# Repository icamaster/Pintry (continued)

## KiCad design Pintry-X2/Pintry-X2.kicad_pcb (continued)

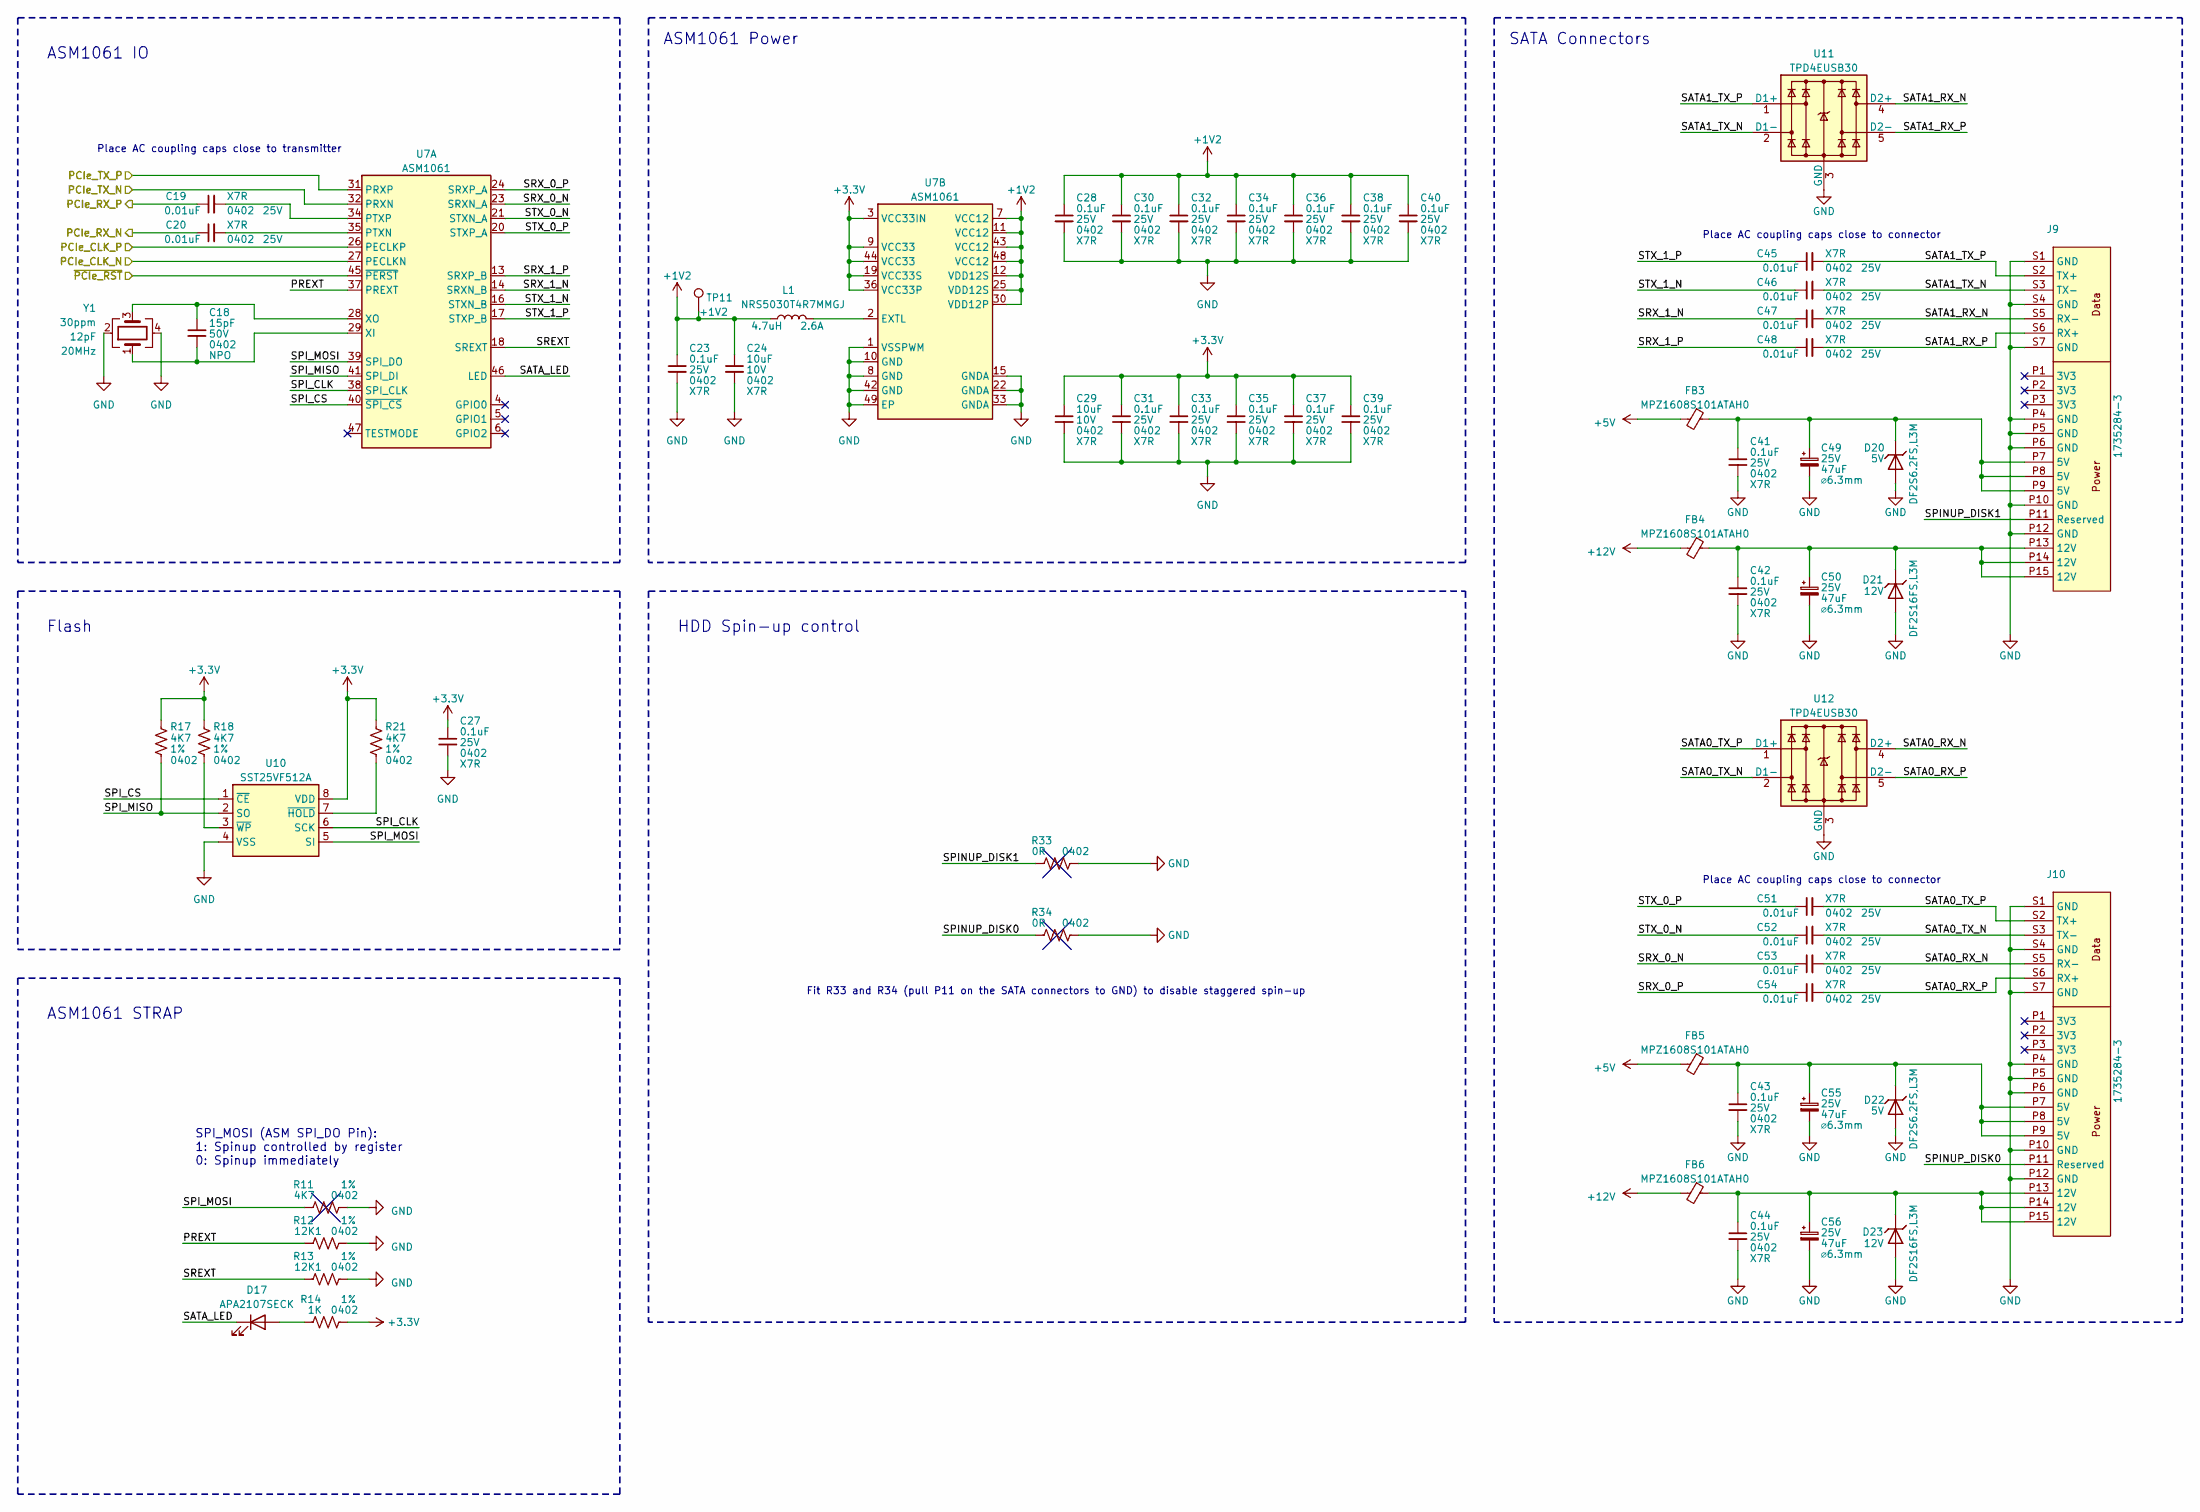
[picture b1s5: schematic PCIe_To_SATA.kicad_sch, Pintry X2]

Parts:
C18: 15pF; C_0402_1005Metric; Voltage Rating 50V
C19, C20, C45, C46, C47, C48, C51, C52, C53, C54: 0.01uF; C_0402_1005Metric; Voltage Rating 25V
C23, C27, C28, C30, C31, C32, C33, C34, C35, C36, C37, C38, C39, C40, C41, C42, C43, C44: 0.1uF; C_0402_1005Metric; Voltage Rating 25V
C24, C29: 10uF; C_0402_1005Metric; Voltage Rating 10V
C49, C50, C55, C56: 865080443007; CP_Elec_6.3x5.4; Voltage 25V; Part Number 865080443007
D17: APA2107SECK; PartNumber APA2107SECK/J4-PRV
D20, D22: DF2S6.2FS,L3M; D_SOD-923; Part Number DF2S6.2FS,L3M
D21, D23: DF2S16FS,L3M; D_SOD-923; Part Number DF2S16FS,L3M
FB3, FB4, FB5, FB6: MPZ1608S101ATAH0; L_0603_1608Metric; Part Number MPZ1608S101ATAH0
J9, J10: 1735284-3; TE_1735284-3; Part Number 1735284-3
L1: NRS5030T4R7MMGJ; L_Taiyo-Yuden_NR-50xx; Current Rating 2.6A; Part Number NRS5030T4R7MMGJ
R11, R17, R18, R21: 4K7; R_0402_1005Metric; Tolerance 1%
R12, R13: 12K1; R_0402_1005Metric; Tolerance 1%
R14: 1K; R_0402_1005Metric; Tolerance 1%
R33, R34: 0R; R_0402_1005Metric; Tolerance 1%
TP11: +1V2; TestPoint_Pad_D1.0mm
U7: ASM1061; QFN-48-1EP_7x7mm_P0.5mm_EP4.025x4.025mm
U10: SST25VF512A; SOIC-8_3.9x4.9mm_P1.27mm; Part Number SST25VF512A-33-4I-SAE-T
U11, U12: TPD4EUSB30; USON-10_2.5x1.0mm_P0.5mm; Part Number TPD4EUSB30DQAR
Y1: ECS-200-12-33-AGN-TR; Crystal_SMD_3225-4Pin_3.2x2.5mm; Part Number ECS-200-12-33-AGN-TR

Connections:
+1V2: C23.1, C24.1, C28.1, C30.1, C32.1, C34.1, C36.1, C38.1, C40.1, L1.1, TP11.1, U7.7 (VCC12), U7.11 (VCC12), U7.12 (VDD12S), U7.25 (VDD12S), U7.30 (VDD12P), U7.43 (VCC12), U7.48 (VCC12)
+3V3: C27.1, C29.1, C31.1, C33.1, C35.1, C37.1, C39.1, R14.2, R17.1, R18.1, R21.1, U7.3 (VCC33IN), U7.9 (VCC33), U7.19 (VCC33S), U7.36 (VCC33P), U7.44 (VCC33), U10.8 (VDD); also elsewhere on the board
+5V: FB3.2, FB5.2; also elsewhere on the board
+12V: FB4.2, FB6.2; also elsewhere on the board
/CM4-USB-PCIe/PCIe_CLK_N: U7.27 (PECLKN); also elsewhere on the board
/CM4-USB-PCIe/PCIe_CLK_P: U7.26 (PECLKP); also elsewhere on the board
/CM4-USB-PCIe/PCIe_RX_N: C20.1; also elsewhere on the board
/CM4-USB-PCIe/PCIe_RX_P: C19.1; also elsewhere on the board
/CM4-USB-PCIe/PCIe_TX_N: U7.32 (PRXN); also elsewhere on the board
/CM4-USB-PCIe/PCIe_TX_P: U7.31 (PRXP); also elsewhere on the board
/CM4-USB-PCIe/~PCIe_RST: U7.45 (~PERST); also elsewhere on the board
/PCIe to SATA/PREXT: R12.1, U7.37 (PREXT)
/PCIe to SATA/SATA0_RX_N: C53.2, J10.S5 (RX-), U12.4 (D2+), U12.7
/PCIe to SATA/SATA0_RX_P: C54.2, J10.S6 (RX+), U12.5 (D2-), U12.6
/PCIe to SATA/SATA0_TX_N: C52.2, J10.S3 (TX-), U12.2 (D1-), U12.9
/PCIe to SATA/SATA0_TX_P: C51.2, J10.S2 (TX+), U12.1 (D1+), U12.10
/PCIe to SATA/SATA1_RX_N: C47.2, J9.S5 (RX-), U11.4 (D2+), U11.7
/PCIe to SATA/SATA1_RX_P: C48.2, J9.S6 (RX+), U11.5 (D2-), U11.6
/PCIe to SATA/SATA1_TX_N: C46.2, J9.S3 (TX-), U11.2 (D1-), U11.9
/PCIe to SATA/SATA1_TX_P: C45.2, J9.S2 (TX+), U11.1 (D1+), U11.10
/PCIe to SATA/SATA_LED: D17.1 (K), U7.46 (LED)
/PCIe to SATA/SPINUP_DISK0: J10.P11 (Reserved), R34.1
/PCIe to SATA/SPINUP_DISK1: J9.P11 (Reserved), R33.1
/PCIe to SATA/SPI_CLK: U7.38 (SPI_CLK), U10.6 (SCK)
/PCIe to SATA/SPI_CS: U7.40 (~SPI_CS), U10.1 (~CE)
/PCIe to SATA/SPI_MISO: R17.2, U7.41 (SPI_DI), U10.2 (SO)
/PCIe to SATA/SPI_MOSI: R11.1, U7.39 (SPI_DO), U10.5 (SI)
/PCIe to SATA/SREXT: R13.1, U7.18 (SREXT)
/PCIe to SATA/SRX_0_N: C53.1, U7.23 (SRXN_A)
/PCIe to SATA/SRX_0_P: C54.1, U7.24 (SRXP_A)
/PCIe to SATA/SRX_1_N: C47.1, U7.14 (SRXN_B)
/PCIe to SATA/SRX_1_P: C48.1, U7.13 (SRXP_B)
/PCIe to SATA/STX_0_N: C52.1, U7.21 (STXN_A)
/PCIe to SATA/STX_0_P: C51.1, U7.20 (STXP_A)
/PCIe to SATA/STX_1_N: C46.1, U7.16 (STXN_B)
/PCIe to SATA/STX_1_P: C45.1, U7.17 (STXP_B)
GND: C23.2, C24.2, C27.2, C28.2, C29.2, C30.2, C31.2, C32.2, C33.2, C34.2, C35.2, C36.2, C37.2, C38.2, C39.2, C40.2, C41.2, C42.2, C43.2, C44.2, C49.2, C50.2, C55.2, C56.2, D20.2 (A), D21.2 (A), D22.2 (A), D23.2 (A), J9.P4 (GND), J9.P5 (GND), J9.P6 (GND), J9.P10 (GND), J9.P12 (GND), J9.S1 (GND), J9.S4 (GND), J9.S7 (GND), J10.P4 (GND), J10.P5 (GND), J10.P6 (GND), J10.P10 (GND), J10.P12 (GND), J10.S1 (GND), J10.S4 (GND), J10.S7 (GND), R11.2, R12.2, R13.2, R33.2, R34.2, U7.1 (VSSPWM), U7.8 (GND), U7.10 (GND), U7.15 (GNDA), U7.22 (GNDA), U7.33 (GNDA), U7.42 (GND), U7.49 (EP), U10.4 (VSS), U11.3 (GND), U11.8 (GND), U12.3 (GND), U12.8 (GND), Y1.2, Y1.4; also elsewhere on the board
unnamed: C18.1, U7.28 (XO), Y1.3
unnamed: C18.2, U7.29 (XI), Y1.1
unnamed: C19.2, U7.34 (PTXP)
unnamed: C20.2, U7.35 (PTXN)
unnamed: C41.1, C49.1, D20.1 (K), FB3.1, J9.P7 (5V), J9.P8 (5V), J9.P9 (5V)
unnamed: C42.1, C50.1, D21.1 (K), FB4.1, J9.P13 (12V), J9.P14 (12V), J9.P15 (12V)
unnamed: C43.1, C55.1, D22.1 (K), FB5.1, J10.P7 (5V), J10.P8 (5V), J10.P9 (5V)
unnamed: C44.1, C56.1, D23.1 (K), FB6.1, J10.P13 (12V), J10.P14 (12V), J10.P15 (12V)
unnamed: D17.2 (A), R14.1
unnamed: L1.2, U7.2 (EXTL)
unnamed: R18.2, U10.3 (~WP)
unnamed: R21.2, U10.7 (~HOLD)

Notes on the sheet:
SATA Connectors
ASM1061 STRAP
ASM1061 IO
Flash
Place AC coupling caps close to transmitter
SPI_MOSI (ASM SPI_DO Pin): 1: Spinup controlled by register 0: Spinup immediately
HDD Spin-up control
Place AC coupling caps close to connector
Fit R33 and R34 (pull P11 on the SATA connectors to GND) to disable staggered spin-up
ASM1061 Power

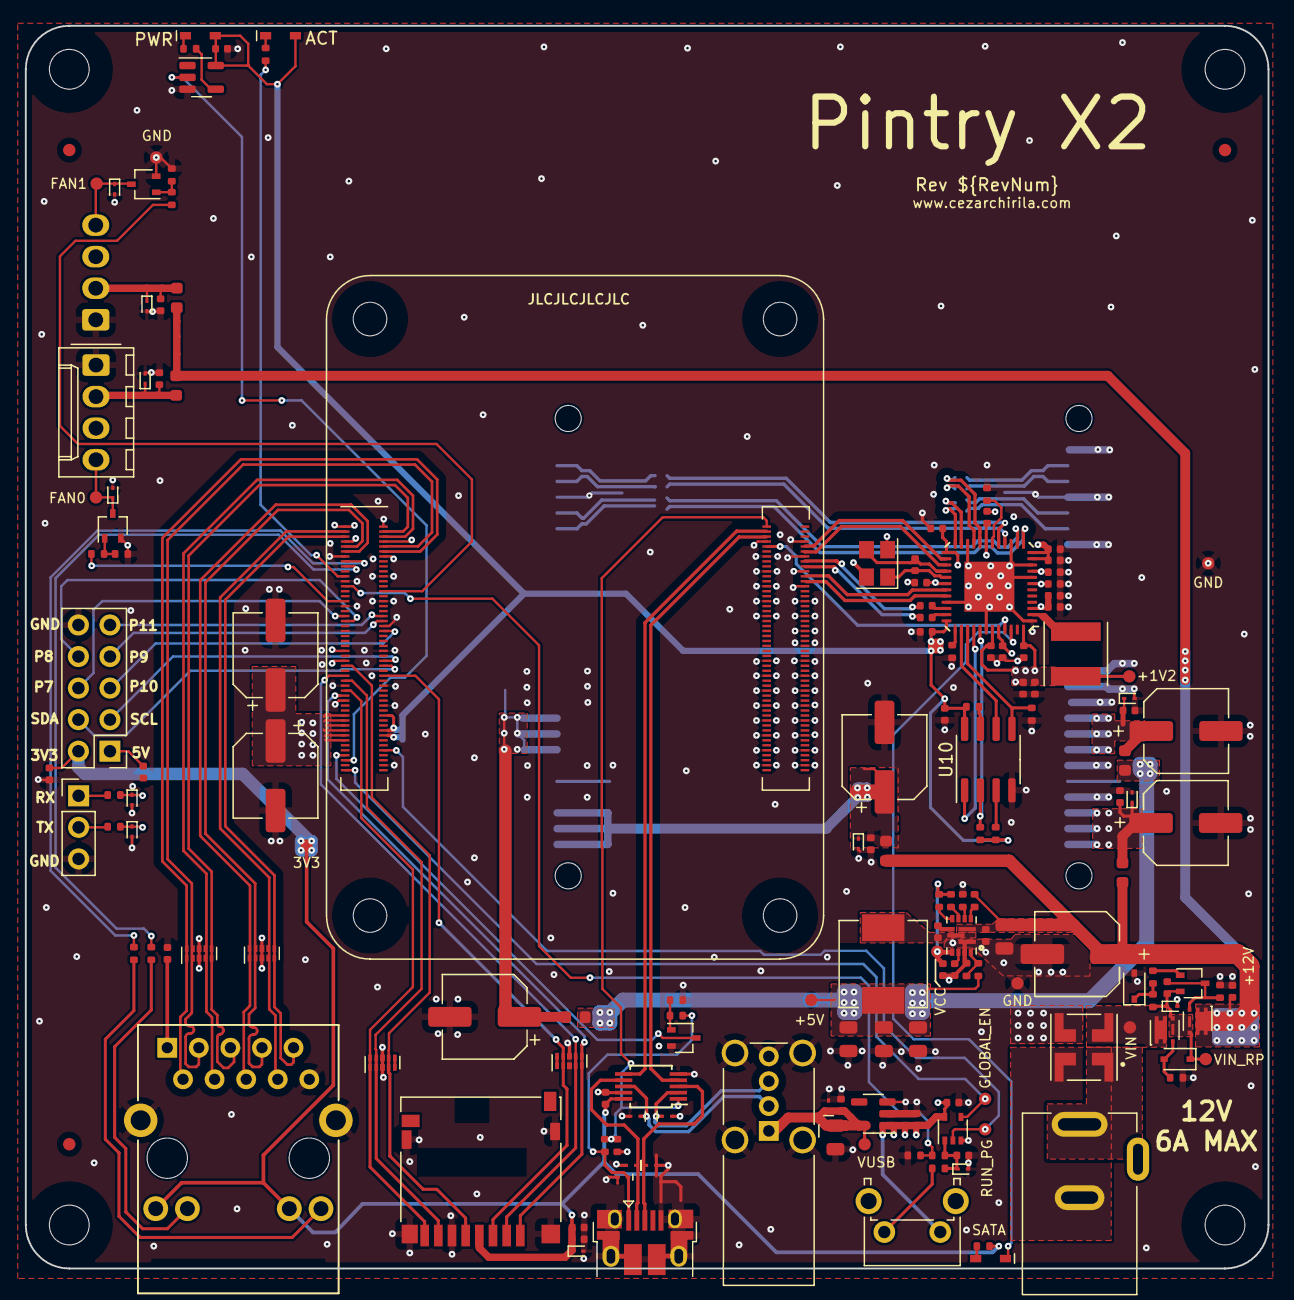
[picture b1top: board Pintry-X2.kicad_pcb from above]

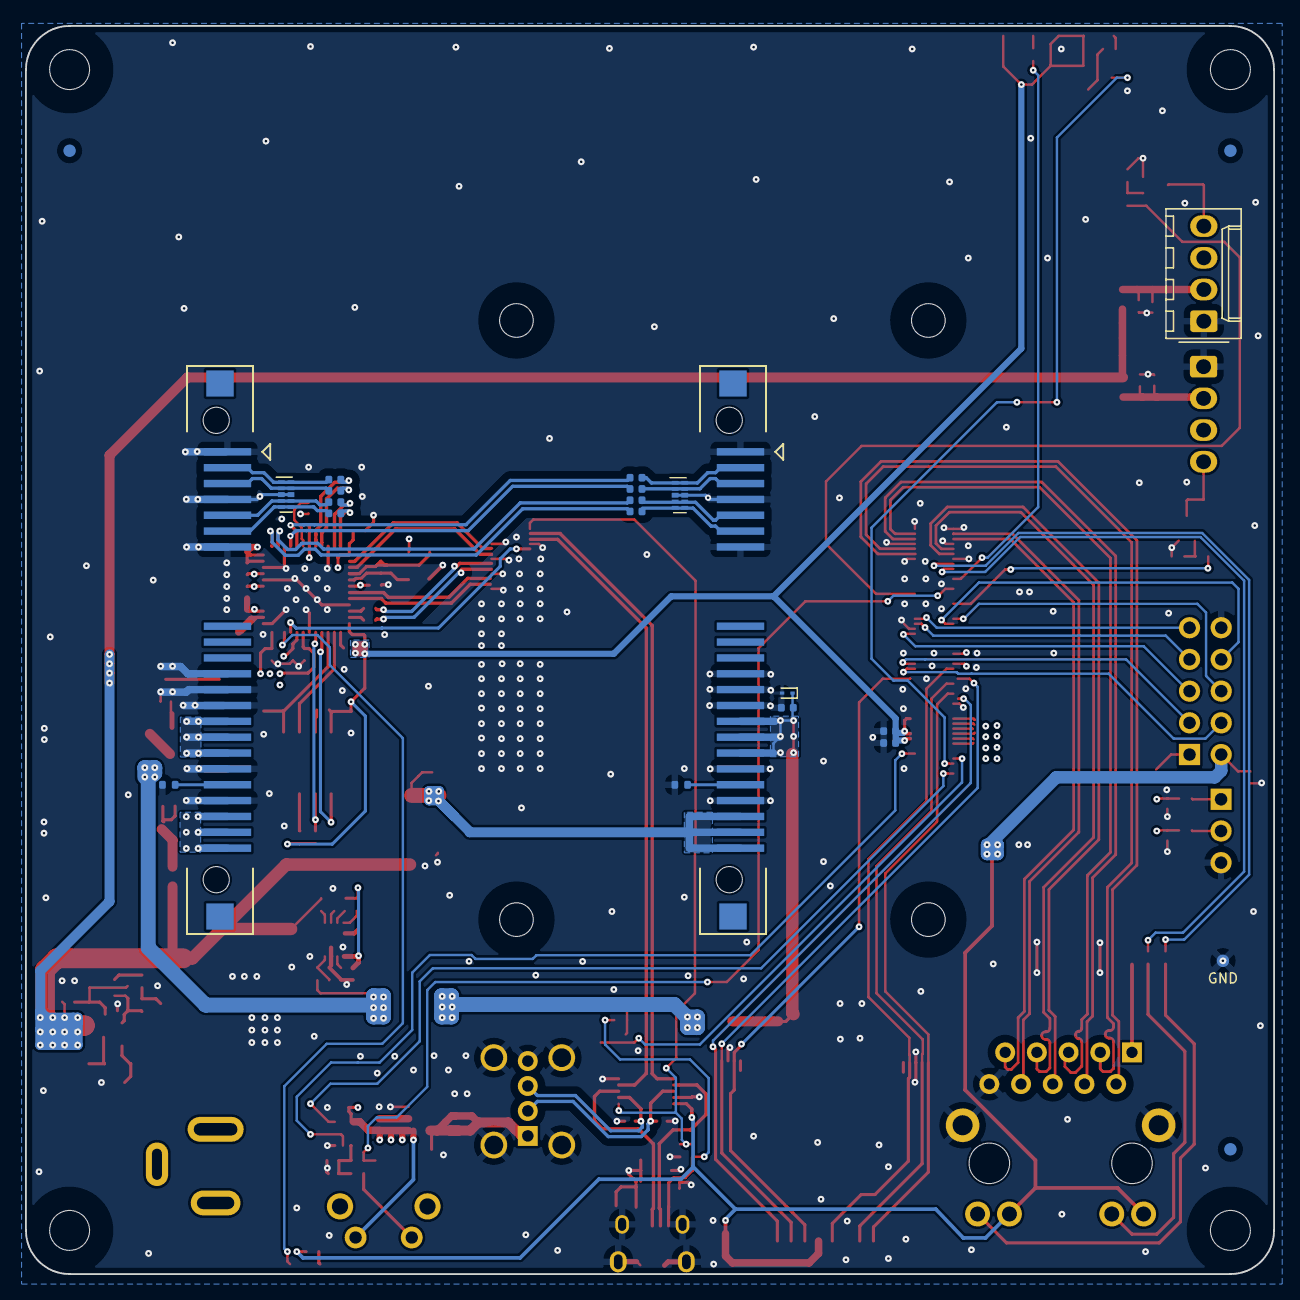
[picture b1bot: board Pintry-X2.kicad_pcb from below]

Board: 4 copper layers, 100.0 x 100.0 mm, 193 parts (23 on the bottom side), 125 nets.

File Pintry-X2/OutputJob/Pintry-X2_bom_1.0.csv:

Component,Description,References,Value,Quantity Per PCB,Manufacturer,Part Number,Voltage Rating,Type,fit_field
1,"Unpolarized capacitor, small symbol",C18,15pF,1,,,50V,NPO,
2,"Unpolarized capacitor, small symbol",C19 C20 C45 C46 C47 C48 C51 C52 C53 C54,0.01uF,10,,,25V,X7R,
3,"Unpolarized capacitor, small symbol",C2 C3 C4 C7 C9 C11 C12 C13 C15 C23 C27 C28 C30 C31 C32 C33 C34 C35 C36 C37 C38 C39 C40 C41 C42 C43 C44 C57 C60 C65,0.1uF,30,,,25V,X7R,
4,"Unpolarized capacitor, small symbol",C61,1uF,1,,,25V,X7R,
5,"Unpolarized capacitor, small symbol",C1 C5 C14 C16 C17 C24 C29 C67 C68,10uF,9,,,10V,X7R,
6,"Unpolarized capacitor, small symbol",C58,22uF,1,Samsung,CL21A226MOQNNNE,16V,X7R,
7,"Unpolarized capacitor, small symbol",C6 C62 C63 C64,22uF,4,Murata,GRM21BR61A226ME51L,16V,X7R,
8,"Polarized capacitor, small symbol",C8 C10 C49 C50 C55 C56 C66,865080443007,7,Wurth,865080443007,,,
9,"Unpolarized capacitor, small symbol",C59,TBD,1,,,25V,X7R,dnf
10,LED Orange Clear,D9 D17,APA2107SECK,2,Kingbright,APA2107SECK/J4-PRV,,,
11,LED Orange Clear,D8,APA2107SECK,1,Kingbright,APA2107SECK/J4-PRV,,,
12,"300mW Zener Diode, SOD-323",D24 D26,BZX384-B13,2,Nexperia,"BZX384-B13,115",,,
13,Diode TVS 3V3,D3 D4 D5 D6 D7 D10 D11 D12,D3V3M1U259-7,8,Diodes,D3V3M1U2S9-7,,,
14,Diode,D13 D14 D21 D23 D25,"DF2S16FS,L3M",5,Toshiba,"DF2S16FS,L3M",,,
15,Diode,D1 D2 D15 D16 D20 D22,"DF2S6.2FS,L3M",6,Toshiba,"DF2S6.2FS,L3M",,,
16,"Ferrite bead, small symbol",FB1 FB2 FB3 FB4 FB5 FB6,MPZ1608S101ATAH0,6,TDK,MPZ1608S101ATAH0,,,
17,"Common mode choke, 300mA, 300VAC, 22mH, 1.3 ohm, RN-102",FL1,DLW5BTM101SQ2L,1,Murata,DLW5BTM101SQ2L,,,
18,SATA Backplane Receptacle Vertical SMT,J9 J10,1735284-3,2,TE Connectivity,1735284-3,,,
19,DC Barrel Jack with an internal switch,J11,54-00131,1,Tensility,54-00131,,,
20,Micro SD Card Socket with card detection pins,J4,DM3D-SF,1,Hirose,DM3D-SF,,,
21,"Generic connector, double row, 02x05, odd/even pin numbering scheme (row 1 odd numbers, row 2 even numbers), script generated (kicad-library-utils/schlib/autogen/connector/)",J6,Expansion,1,Adam Tech,2PH2-10-UA,,,
22,"Generic connector, single row, 01x04, script generated (kicad-library-utils/schlib/autogen/connector/)",J7 J8,Fan,2,Molex,0022232031,,,
23,"LAN Transformer Jack, RJ45, 10/100/1000 BaseT",J3,JD0-0001NL,1,Pulse,JD0-0001NL,,,
24,"Generic connector, single row, 01x03, script generated (kicad-library-utils/schlib/autogen/connector/)",J5,UART,1,Adam Tech,PH1-03-UA,,,
25,USB Type A connector,J2,USB_A,1,Amphenol ICC,73725-11A0BLF,,,
26,USB Micro Type B connector,J1,USB_B_Micro,1,Amphenol ICC,10103594-0001LF,,,
27,4.7µH Shielded Wirewound Inductor 2.6A 35mOhm,L1,NRS5030T4R7MMGJ,1,Taiyo Yuden,NRS5030T4R7MMGJ,,,
28,1.2µH Shielded Molded Inductor 10A 12mOhm,L2,PA4341.122NLT,1,Pulse,PA4341.122NLT,,,
29,,Module1,ComputeModule4-CM4,1,Hirose,2x DF40C-100DS-0.4V,,,
30,"PNP transistor, base/emitter/collector",Q6,BC857BW,1,Nexperia,"BC857BW,135",,,
31,"N-MOSFET transistor, gate/source/drain",Q1 Q2 Q3,BSS138PW,3,Nexperia,"BSS138PW,115",,,
32,"-12A Id, -30V Vds, P-Channel MOSFET",Q5,SIA483DJ,1,Vishay,SIA483DJ-T1-GE3,,,
33,"-12A Id, -30V Vds, P-Channel MOSFET",Q7,SIA483DJ,1,Vishay,SIA483DJ-T1-GE3,,,
34,"Resistor, US symbol",R33 R34,0R,2,,,,,dnf
35,"Resistor, US symbol",R3 R4,470R,2,,,,,
36,"Resistor, US symbol",R1 R6 R19 R20,1K,4,,,,,
37,"Resistor, US symbol",R2 R5 R7 R8 R11 R14 R16 R17 R18 R21 R27 R28 R32,4K7,13,,,,,dnf
38,"Resistor, US symbol",R12 R13,12K1,2,,,,,
39,"Resistor, US symbol",R30,30K1,1,,,,,
40,"Resistor, US symbol",R9 R10 R15 R22 R23 R24 R25 R26 R31 R35,100K,10,,,,,dnf
41,"Resistor, US symbol",R29,221K,1,,,,,
42,"Push button switch, generic, two pins",SW1,SW_Push,1,TE Connectivity,1-1825027-4,,,
43,"Single Buffer Gate Tri-State, Low-Voltage CMOS",U4,74AHCT1G126,1,Diodes,74AHCT1G126SE-7,,,
44,"4.5V TO 18V INPUT, 6A SYNCHRONOUS BUCK CONVERTER",U13,AP62600,1,Diodes,AP62600SJ-7,,,
45,PCI Express 2.0 to 2 x SATA 6Gbps Controller,U7,ASM1061,1,ASMedia,ASM1061,,,
46,USB Switch IC 1 Channel 10-MSOP,U14,FSUSB30MUX,1,ON Semiconductor,FSUSB30MUX,,,
47,,U15,MIC2005-0.5LYM5,1,Microchip,MIC2005-0.5LYM5,,,
48,"Single Schmitt Buffer Gate, Low-Voltage CMOS",U3,SN74LVC1G17,1,Texas Instruments,SN74LVC1G17DBVR,,,
49,"8-Mbit, 2.7 to 3.6V, SPI Flash Memory, SOIC-8",U10,SST25VF512A,1,Microchip,SST25VF512A-33-4I-SAE-T,,,
50,"4-Channel ESD Protection for Super-Speed USB 3.0 Interface, USON-10",U1 U2 U5 U6 U11 U12,TPD4EUSB30,6,Texas Instruments,TPD4EUSB30DQAR,,,
51,"Four pin crystal, GND on pins 2 and 4",Y1,ECS-200-12-33-AGN-TR,1,ECS,ECS-200-12-33-AGN-TR,,,





Component Groups:,51
Component Count:,165
Fitted Components:,165
Number of PCBs:,1
Total components:,165
Schematic Version:,1.0
Schematic Date:,
PCB Variant:,default
BoM Date:,23/10/2021 22:58:01
Schematic Source:,Pintry-X2.kicad_sch
KiCad Version:,Eeschema (5.99.0-12650-g5c402a64ab)

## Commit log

2021-05-30 Initialise Project
2021-05-30 Add README
2021-05-30 Add License
2021-06-25 Bunch of shit done, probably should commit
2021-06-25 Explain stupid name
2021-06-26 Cleaned up schematic
2021-07-04 Finished Shematic. Starting PCB
2021-10-20 PCB Routing Complete - needs review
2021-10-23 Final touches and generate Gerbers to be sent to fab
2021-11-27 Updated to Rev 1.1. Added interactive HTML
2021-11-27 Update path for Interactive BOM
2021-11-28 Fixed ON/OFF Button
2021-11-28 Remove OutputJob
2021-12-20 Moved ethernet connector so that it sticks out a bit
2021-12-20 Improved DRC routing. Removed DTO files.
2021-12-30 Release version 1.1
